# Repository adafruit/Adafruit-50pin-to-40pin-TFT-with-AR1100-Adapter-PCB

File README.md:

## Adafruit 50pin to 40pin TFT with AR1100 Adapter PCB
<a href="http://www.adafruit.com/products/3305"><br/>
Click here to purchase one from the Adafruit shop
</a>

PCB files for the Adafruit 50pin to 40pin TFT with AR1100 Adapter
- https://www.adafruit.com/product/3305

Format is EagleCAD schematic and board layout

This is a very special adapter, specifically used for adapting our RTD266X driver boards that have 50-pin TFT connectors to use 40-pin TFTs. Please note the adapter cannot be used the other way around! As an addition, we add in an AR1100 resistive touch controller.

Resistive touch screens are incredibly popular as overlays to TFT and LCD displays. If you want to connect one to a computer you need something to handle the analog to digital conversion. Most converters we've found are not very easy to use, and are 'fixed' - making them difficult to calibrate. The AR1100 is a nice chip that solves this problem by acting as a touch->USB converter and also comes with calibration software. The calibration software is Windows only, but once you've calibrated you can use the screen on any OS. The AR1100 shows up as a regular Mouse or Digitizer HID device so no drivers are required and it works on any operating system that supports a USB mouse.

These are sold with our test calibration, you may need to calibrate yourself which you can do with the Microchip windows software. For more details including calibration software, check out the AR1100 page. Once you've got video working, when you plug into a computer's USB port you should see a new device and touching the screen will cause the mouse cursor to move around.

This adapter is for advanced users only!

### License

Adafruit invests time and resources providing this open source design, please support Adafruit and open-source hardware by purchasing products from [Adafruit.com](https://www.adafruit.com)!

See license.txt for more information.

Creative Commons Attribution, Share-Alike license, check license.txt for more information 
All text above must be included in any redistribution

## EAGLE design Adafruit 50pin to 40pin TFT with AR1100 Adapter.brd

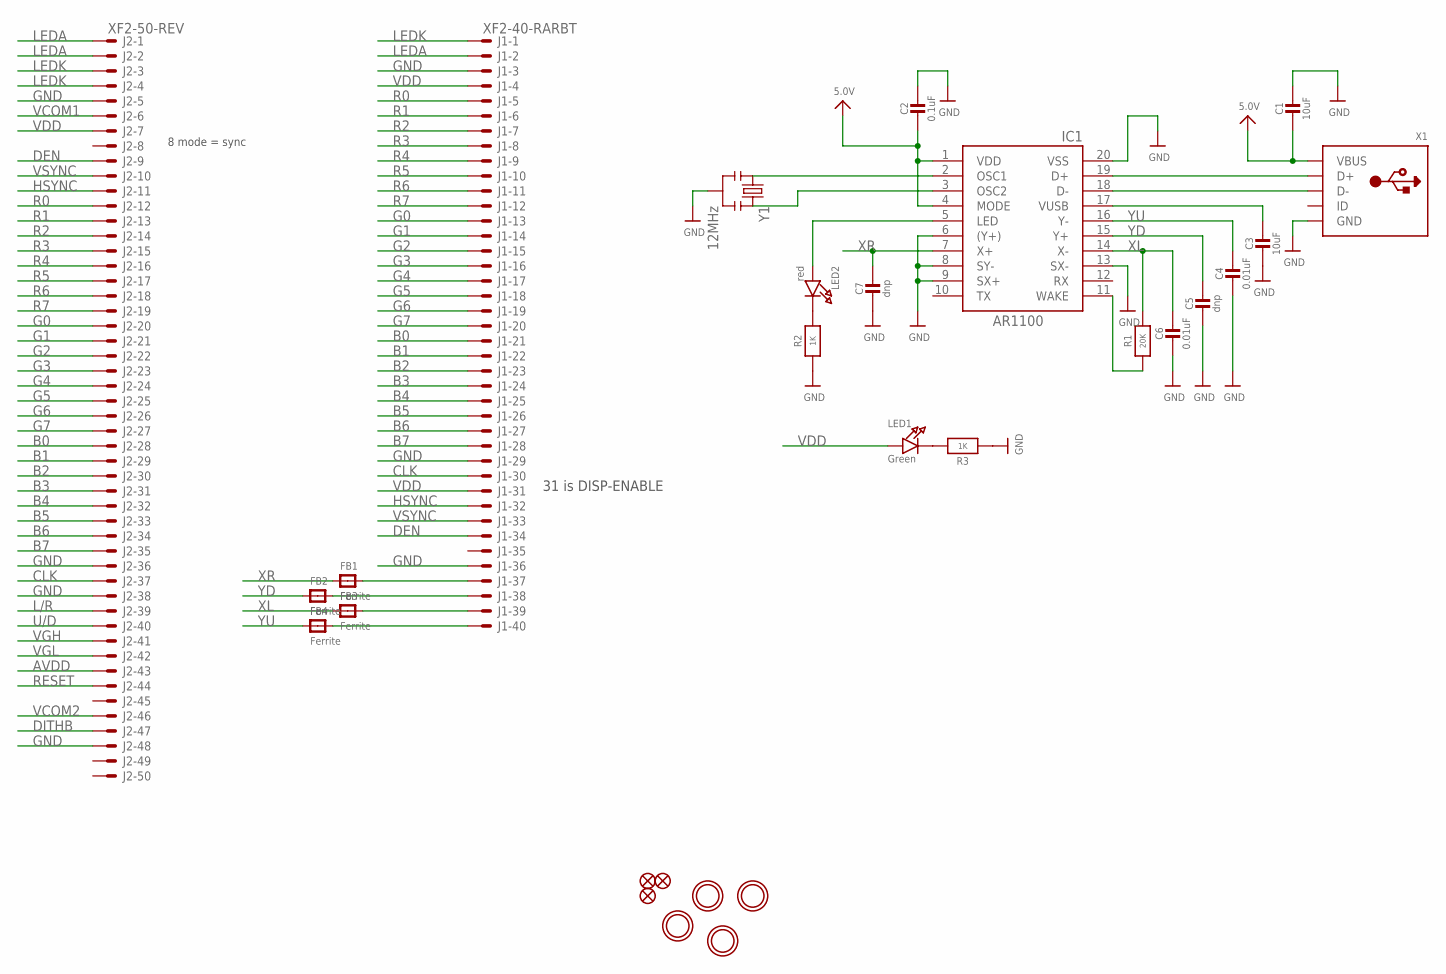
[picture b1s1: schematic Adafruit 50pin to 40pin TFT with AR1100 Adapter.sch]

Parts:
C1, C3: 10uF; _0805MP
C2: 0.1uF; _0805MP
C4, C6: 0.01uF; _0805MP
C5, C7: dnp; _0805MP
FB1, FB2, FB3, FB4: Ferrite; _0805
FID1, FID2, FID3: FIDUCIAL""; FIDUCIAL_1MM
IC1: AR1100_SSOP; TSSOP20-5.3MMBODY
J1: XF2-40-RARBT; 4-1734839-0
J2: XF2-50-REV; 5-1734839-0-REV
LED1: Green; CHIPLED_0805_NOOUTLINE
LED2: red; CHIPLED_0805_NOOUTLINE
R1: 20K; _0805MP
R2, R3: 1K; _0805MP
U$11, U$14, U$15, U$16: MOUNTINGHOLE2.5; MOUNTINGHOLE_2.5_PLATED
X1: USBMINIBLARGE; USB-MINIB_LARGER
Y1: 12MHz; RESONATOR-SMD

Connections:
5.0V: C1.2, C2.2, IC1.1 (VDD), IC1.4 (MODE), X1.VBUS
AVDD: J2.43 (MS)
B0: J1.21 (MS), J2.28 (MS)
B1: J1.22 (MS), J2.29 (MS)
B2: J1.23 (MS), J2.30 (MS)
B3: J1.24 (MS), J2.31 (MS)
B4: J1.25 (MS), J2.32 (MS)
B5: J1.26 (MS), J2.33 (MS)
B6: J1.27 (MS), J2.34 (MS)
B7: J1.28 (MS), J2.35 (MS)
CLK: J1.30 (MS), J2.37 (MS)
D+: IC1.19 (D+), X1.D+
D-: IC1.18 (D-), X1.D-
DEN: J1.34 (MS), J2.9 (MS)
DITHB: J2.47 (MS)
G0: J1.13 (MS), J2.20 (MS)
G1: J1.14 (MS), J2.21 (MS)
G2: J1.15 (MS), J2.22 (MS)
G3: J1.16 (MS), J2.23 (MS)
G4: J1.17 (MS), J2.24 (MS)
G5: J1.18 (MS), J2.25 (MS)
G6: J1.19 (MS), J2.26 (MS)
G7: J1.20 (MS), J2.27 (MS)
GND: C1.1, C2.1, C3.2, C4.2, C5.2, C6.2, C7.2, IC1.6 ((Y+)), IC1.8 (SY-), IC1.9 (SX+), IC1.13 (SX-), IC1.20 (VSS), J1.3 (MS), J1.29 (MS), J1.36 (MS), J2.5 (MS), J2.36 (MS), J2.38 (MS), J2.48 (MS), R2.1, R3.1, X1.GND, X1.GND1 (GND), X1.GND2 (GND), X1.GND3 (GND), X1.GND4 (GND), Y1.2
HSYNC: J1.32 (MS), J2.11 (MS)
L/R: J2.39 (MS)
LEDA: J1.2 (MS), J2.1 (MSV), J2.2 (MS)
LEDK: J1.1 (MSV), J2.3 (MS), J2.4 (MS)
unnamed: IC1.2 (OSC1), Y1.1
unnamed: IC1.3 (OSC2), Y1.3
unnamed: FB1.2, J1.37 (MS)
unnamed: FB2.2, J1.38 (MS)
unnamed: FB3.2, J1.39 (MS)
unnamed: FB4.2, J1.40 (MS)
unnamed: LED2.C, R2.2
unnamed: IC1.5 (LED), LED2.A
unnamed: IC1.11 (WAKE), R1.1
unnamed: LED1.C, R3.2
unnamed: C3.1, IC1.17 (VUSB)
R0: J1.5 (MS), J2.12 (MS)
R1: J1.6 (MS), J2.13 (MS)
R2: J1.7 (MS), J2.14 (MS)
R3: J1.8 (MS), J2.15 (MS)
R4: J1.9 (MS), J2.16 (MS)
R5: J1.10 (MS), J2.17 (MS)
R6: J1.11 (MS), J2.18 (MS)
R7: J1.12 (MS), J2.19 (MS)
RESET: J2.44 (MS)
U/D: J2.40 (MS)
VCOM1: J2.6 (MS)
VCOM2: J2.46 (MS)
VDD: J1.4 (MS), J1.31 (MS), J2.7 (MS), LED1.A
VGH: J2.41 (MS)
VGL: J2.42 (MS)
VSYNC: J1.33 (MS), J2.10 (MS)
XL: C6.1, FB3.1, IC1.14 (X-), R1.2
XR: C7.1, FB1.1, IC1.7 (X+)
YD: C5.1, FB2.1, IC1.15 (Y+)
YU: C4.1, FB4.1, IC1.16 (Y-)

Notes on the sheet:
31 is DISP-ENABLE
8 mode = sync

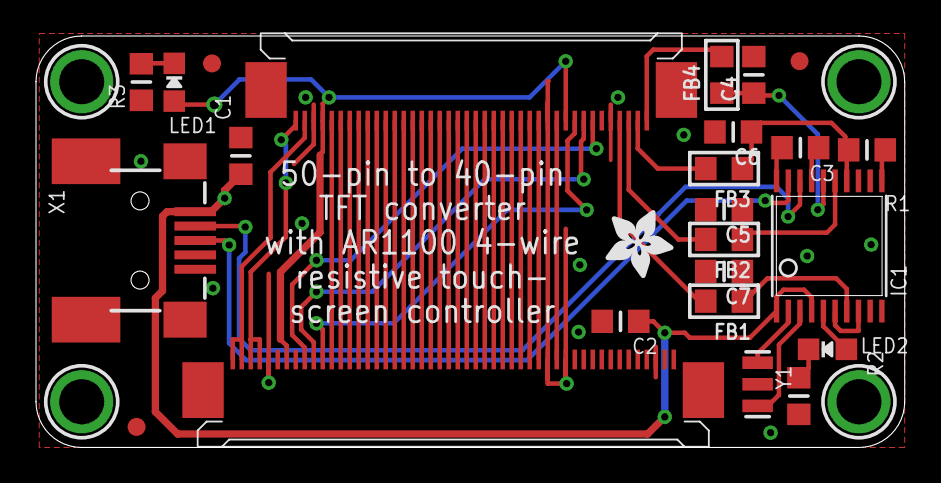
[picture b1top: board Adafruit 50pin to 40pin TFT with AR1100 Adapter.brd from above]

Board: 2 copper layers, 48.3 x 22.9 mm, 30 parts (1 on the bottom side), 50 nets.

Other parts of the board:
U$18: ADAFRUIT_TEXT_30MM
U$19: ADAFRUIT_3.5MM

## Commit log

2016-10-07 init

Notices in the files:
parts and their libraries:
microbuilder: This work is placed in the public domain, and may be freely used for commercial and non-commercial work with the following conditions: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
SparkFun: Licensing: CC v3.0 Share-Alike You are welcome to use this library for commercial purposes.
